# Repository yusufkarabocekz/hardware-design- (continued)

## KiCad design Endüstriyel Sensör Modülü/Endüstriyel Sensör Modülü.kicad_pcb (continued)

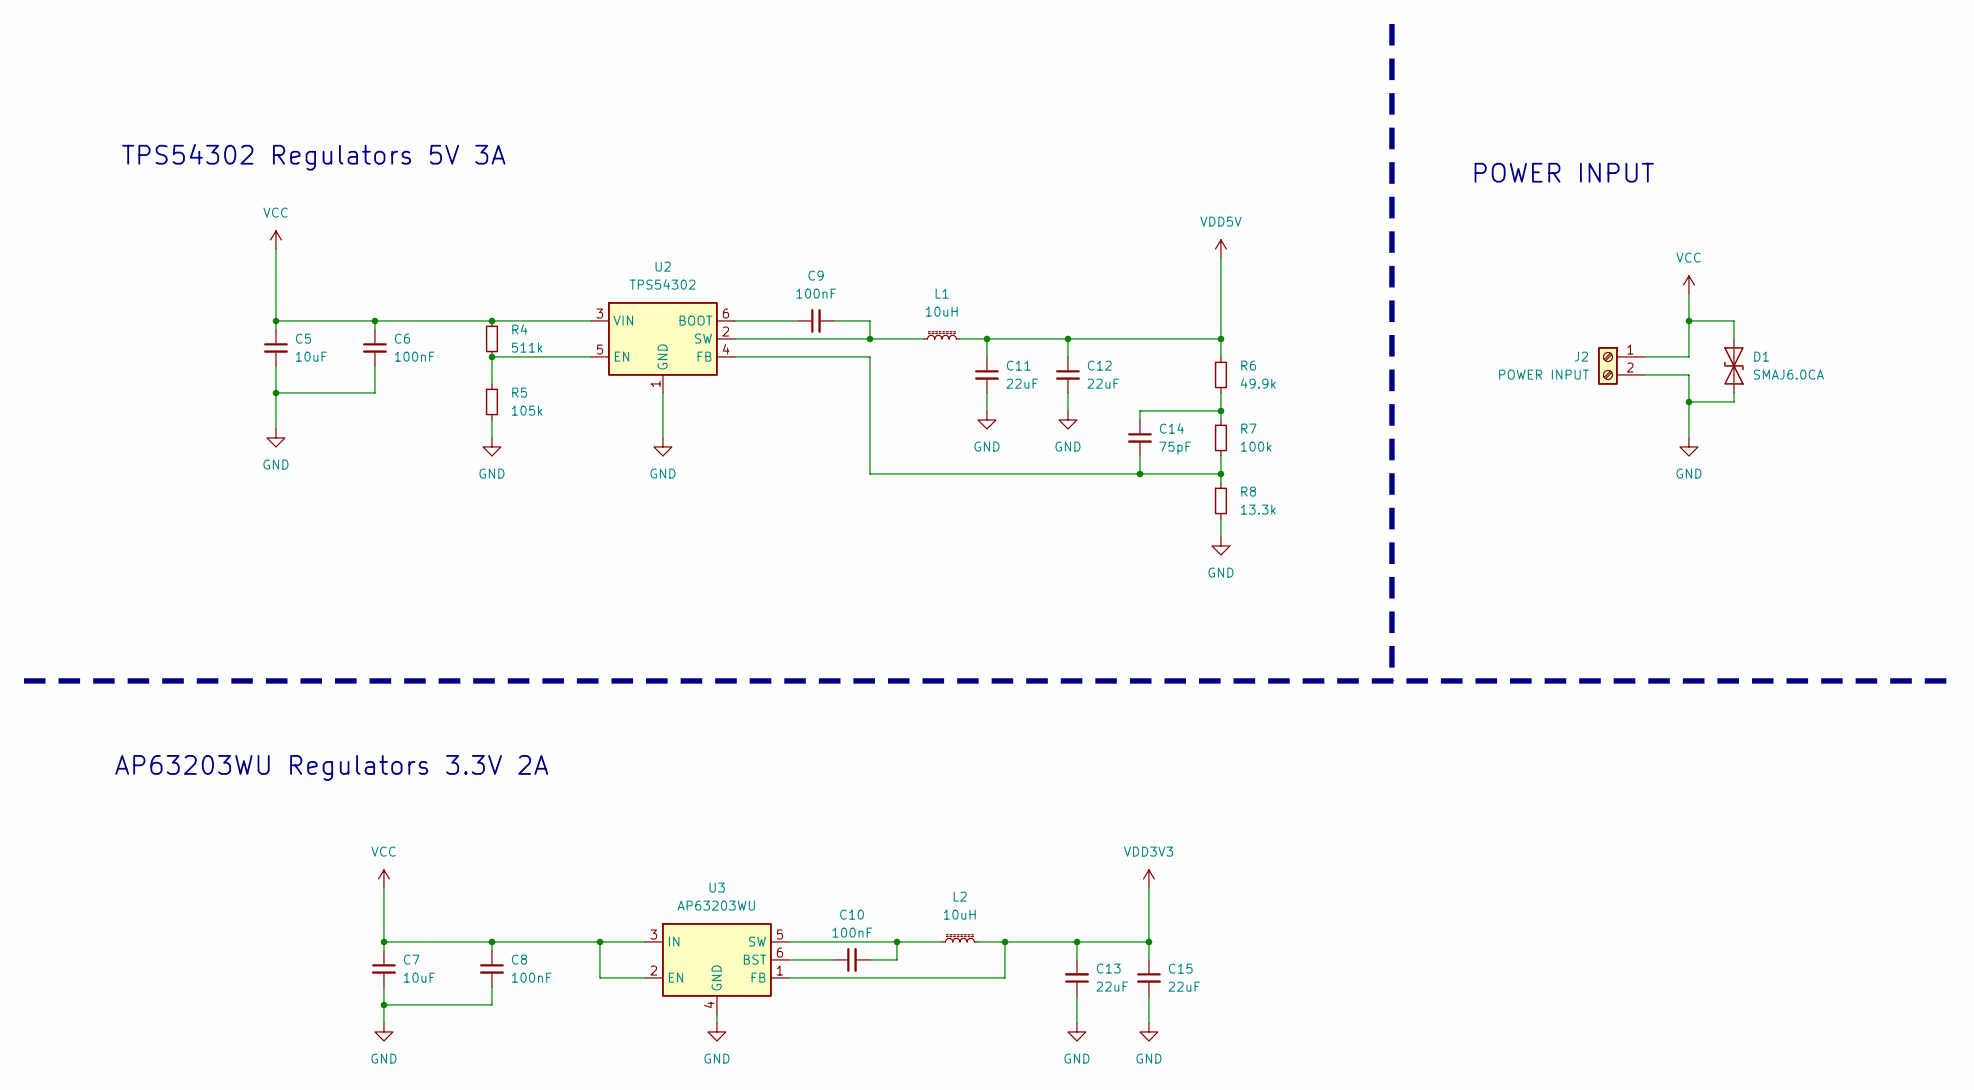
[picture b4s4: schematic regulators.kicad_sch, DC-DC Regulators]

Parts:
C5, C7: 10uF; C_0603_1608Metric
C6, C8, C9, C10: 100nF; C_0603_1608Metric
C11, C12, C13, C15: 22uF; C_0603_1608Metric
C14: 75pF; C_0603_1608Metric
D1: SMAJ6.0CA; D_SMA
J2: POWER INPUT; PhoenixContact_MSTBA_2,5_2-G-5,08_1x02_P5.08mm_Horizontal
L1, L2: 10uH; L_APV_ANR4030
R4: 511k; R_0603_1608Metric
R5: 105k; R_0603_1608Metric
R6: 49.9k; R_0603_1608Metric
R7: 100k; R_0603_1608Metric
R8: 13.3k; R_0603_1608Metric
U2: TPS54302; SOT-23-6
U3: AP63203WU; TSOT-23-6

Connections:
GND: C5.2, C6.2, C7.2, C8.2, C11.2, C12.2, C13.1, C15.2, D1.1 (A1), J2.2, R5.2, R8.2, U2.1 (GND), U3.4 (GND); also elsewhere on the board
unnamed: C14.1, R6.2, R7.1
unnamed: C9.1, U2.6 (BOOT)
unnamed: R4.2, R5.1, U2.5 (EN)
unnamed: C14.2, R7.2, R8.1, U2.4 (FB)
unnamed: C9.2, L1.1, U2.2 (SW)
unnamed: C10.1, U3.6 (BST)
unnamed: C10.2, L2.1, U3.5 (SW)
VCC: C5.1, C6.1, C7.1, C8.1, D1.2 (A2), J2.1, R4.1, U2.3 (VIN), U3.2 (EN), U3.3 (IN)
VDD3V3: C13.2, C15.1, L2.2, U3.1 (FB); also elsewhere on the board
VDD5V: C11.1, C12.1, L1.2, R6.1; also elsewhere on the board

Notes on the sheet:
TPS54302 Regulators 5V 3A
POWER INPUT
AP63203WU Regulators 3.3V 2A

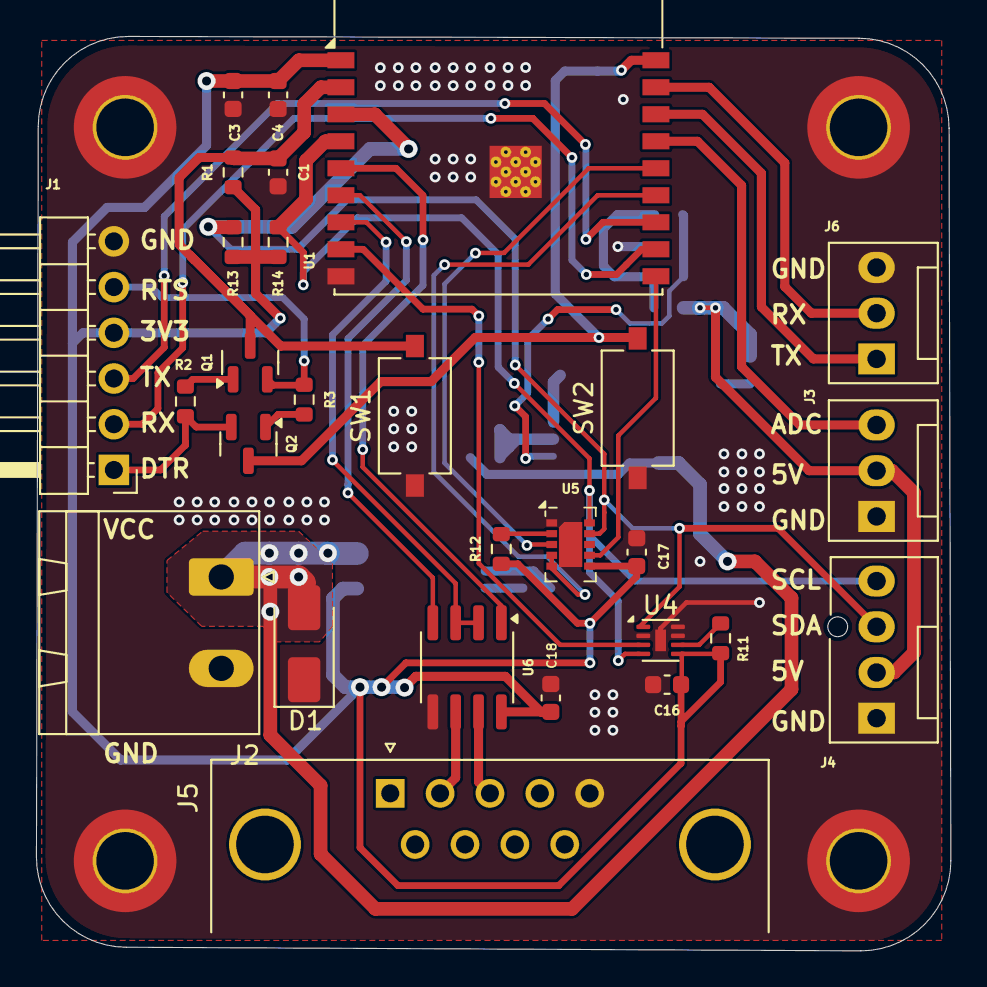
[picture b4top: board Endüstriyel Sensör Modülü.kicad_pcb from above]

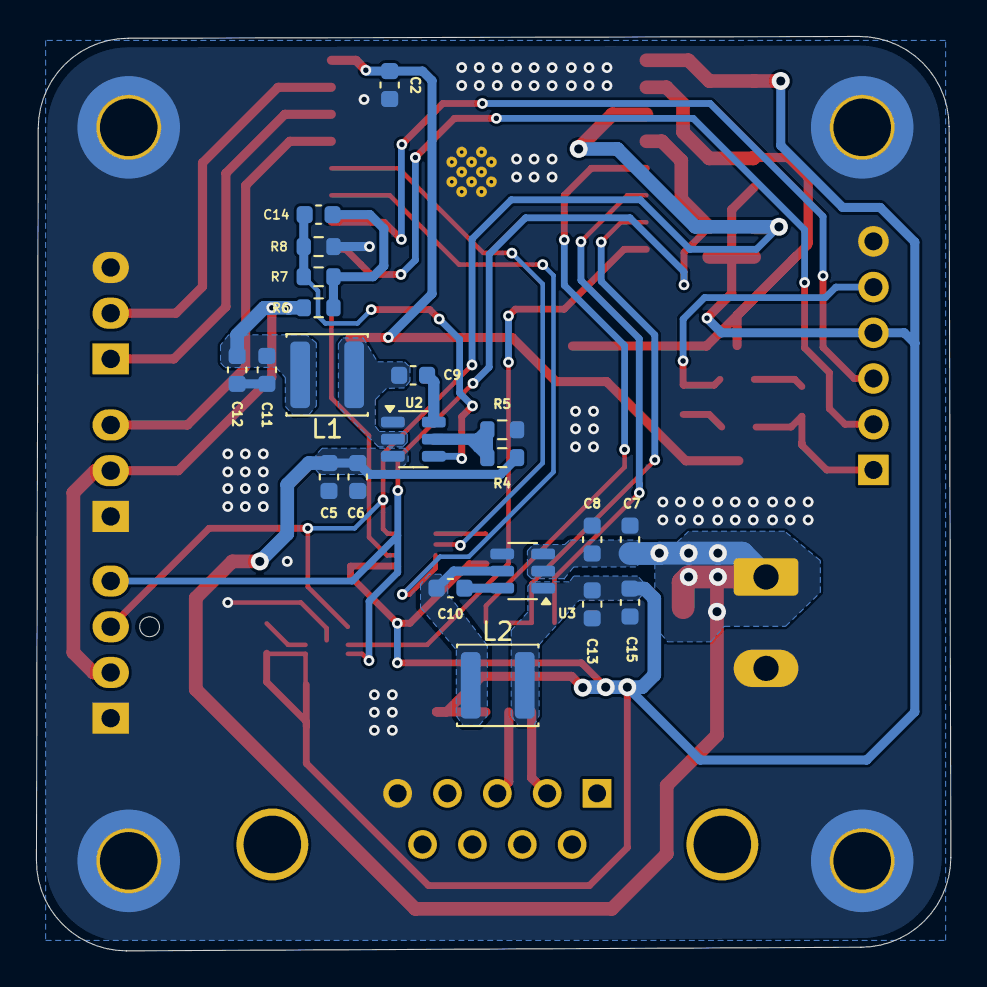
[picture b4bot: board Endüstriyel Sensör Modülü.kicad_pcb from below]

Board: 4 copper layers, 50.8 x 50.8 mm, 53 parts (21 on the bottom side), 35 nets.

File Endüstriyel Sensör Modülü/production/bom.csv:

Designator,Footprint,Quantity,Value,LCSC Part #
"C1, C17",0603,2,1uF,
"C10, C16, C18, C2, C4, C6, C8, C9",0603,8,100nF,
"C11, C12, C13, C15",0603,4,22uF,
C14,0603,1,75pF,
"C3, C5, C7",0603,3,10uF,
D1,D_SMA,1,SMAJ6.0CA,
J1,PinHeader_1x06_P2.54mm_Horizontal,1,FTDI232 Connector,
J2,"PhoenixContact_MSTBA_2,5_2-G-5,08_1x02_P5.08mm_Horizontal",1,POWER INPUT,
J3,FanPinHeader_1x03_P2.54mm_Vertical,1,ADC,
J4,FanPinHeader_1x04_P2.54mm_Vertical,1,I2C,
J5,DSUB-9_Pins_Horizontal_P2.77x2.84mm_EdgePinOffset4.94mm_Housed_MountingHolesOffset4.94mm,1,DE9_Pins,
J6,FanPinHeader_1x03_P2.54mm_Vertical,1,UART,
"L1, L2",L_APV_ANR4030,2,10uH,
"Q1, Q2",SOT-23,2,SS8050,
R1,0603,1,10k,
R11,0603,1,2k,
"R12, R13, R14",0603,3,4.7k,
"R2, R3",0603,2,12k,
R4,0603,1,511k,
R5,0603,1,105k,
R6,0603,1,49.9k,
R7,0603,1,100k,
R8,0603,1,13.3k,
SW1,SW_Tactile_SPST_NO_Straight_CK_PTS636Sx25SMTRLFS,1,RESET,
SW2,SW_Tactile_SPST_NO_Straight_CK_PTS636Sx25SMTRLFS,1,BOOT,
U1,ESP32-C3-WROOM-02,1,ESP32-C3-WROOM-02,
U2,SOT-23-6,1,TPS54302,
U3,TSOT-23-6,1,AP63203WU,
U4,DFN-8-1EP_2x2mm_P0.5mm_EP0.6x1.2mm,1,SHT31A-DIS,
U5,AMS_LGA-10-1EP_2.7x4mm_P0.6mm,1,CCS811,
U6,SOIC-8_3.9x4.9mm_P1.27mm,1,MAX485E,

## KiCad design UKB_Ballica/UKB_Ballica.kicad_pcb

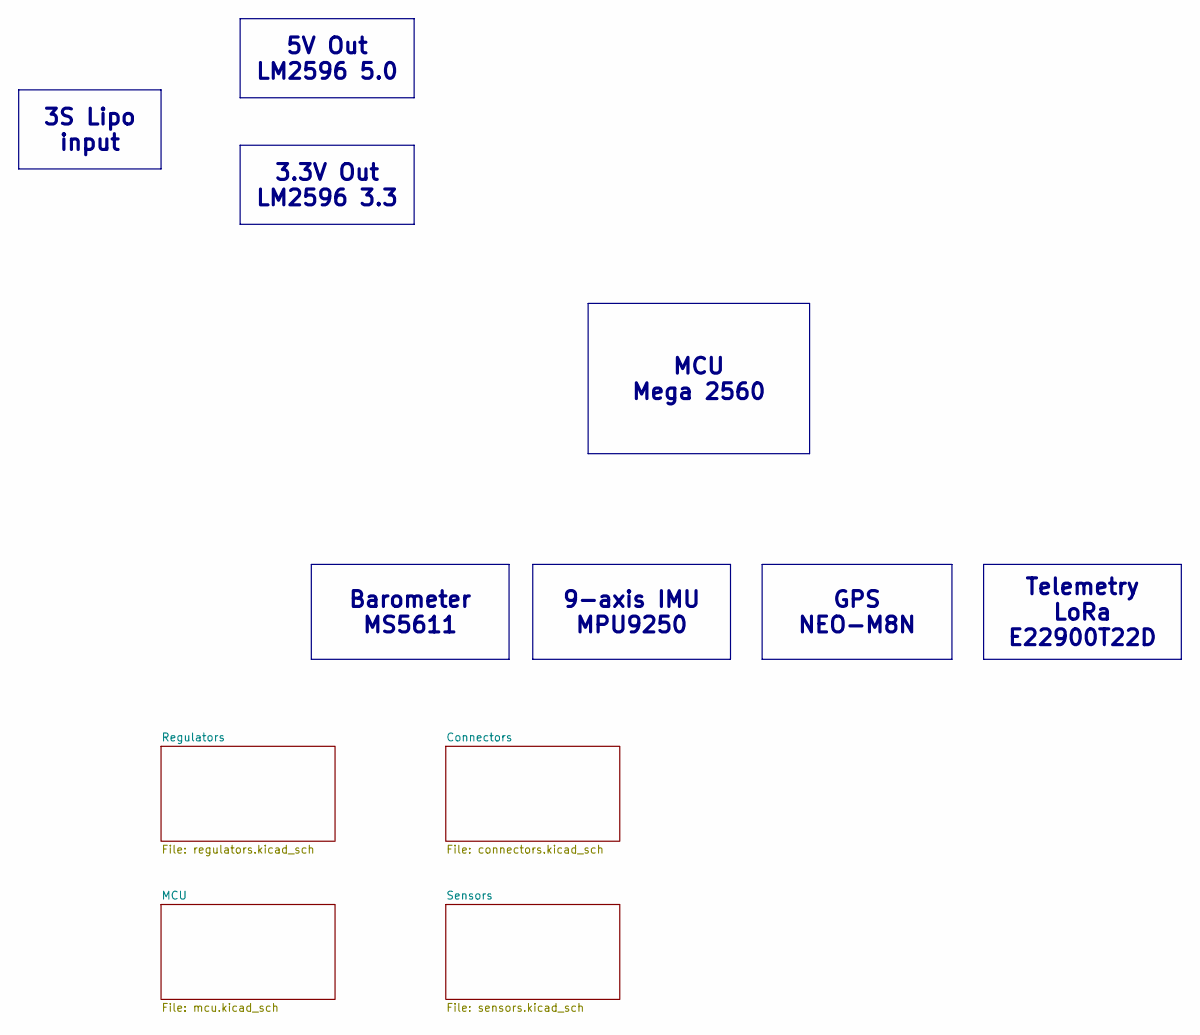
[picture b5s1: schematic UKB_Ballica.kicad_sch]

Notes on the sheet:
Telemetry LoRa E22900T22D
Barometer MS5611
GPS NEO-M8N
5V Out LM2596 5.0
9-axis IMU MPU9250
MCU Mega 2560
3S Lipo input
3.3V Out LM2596 3.3

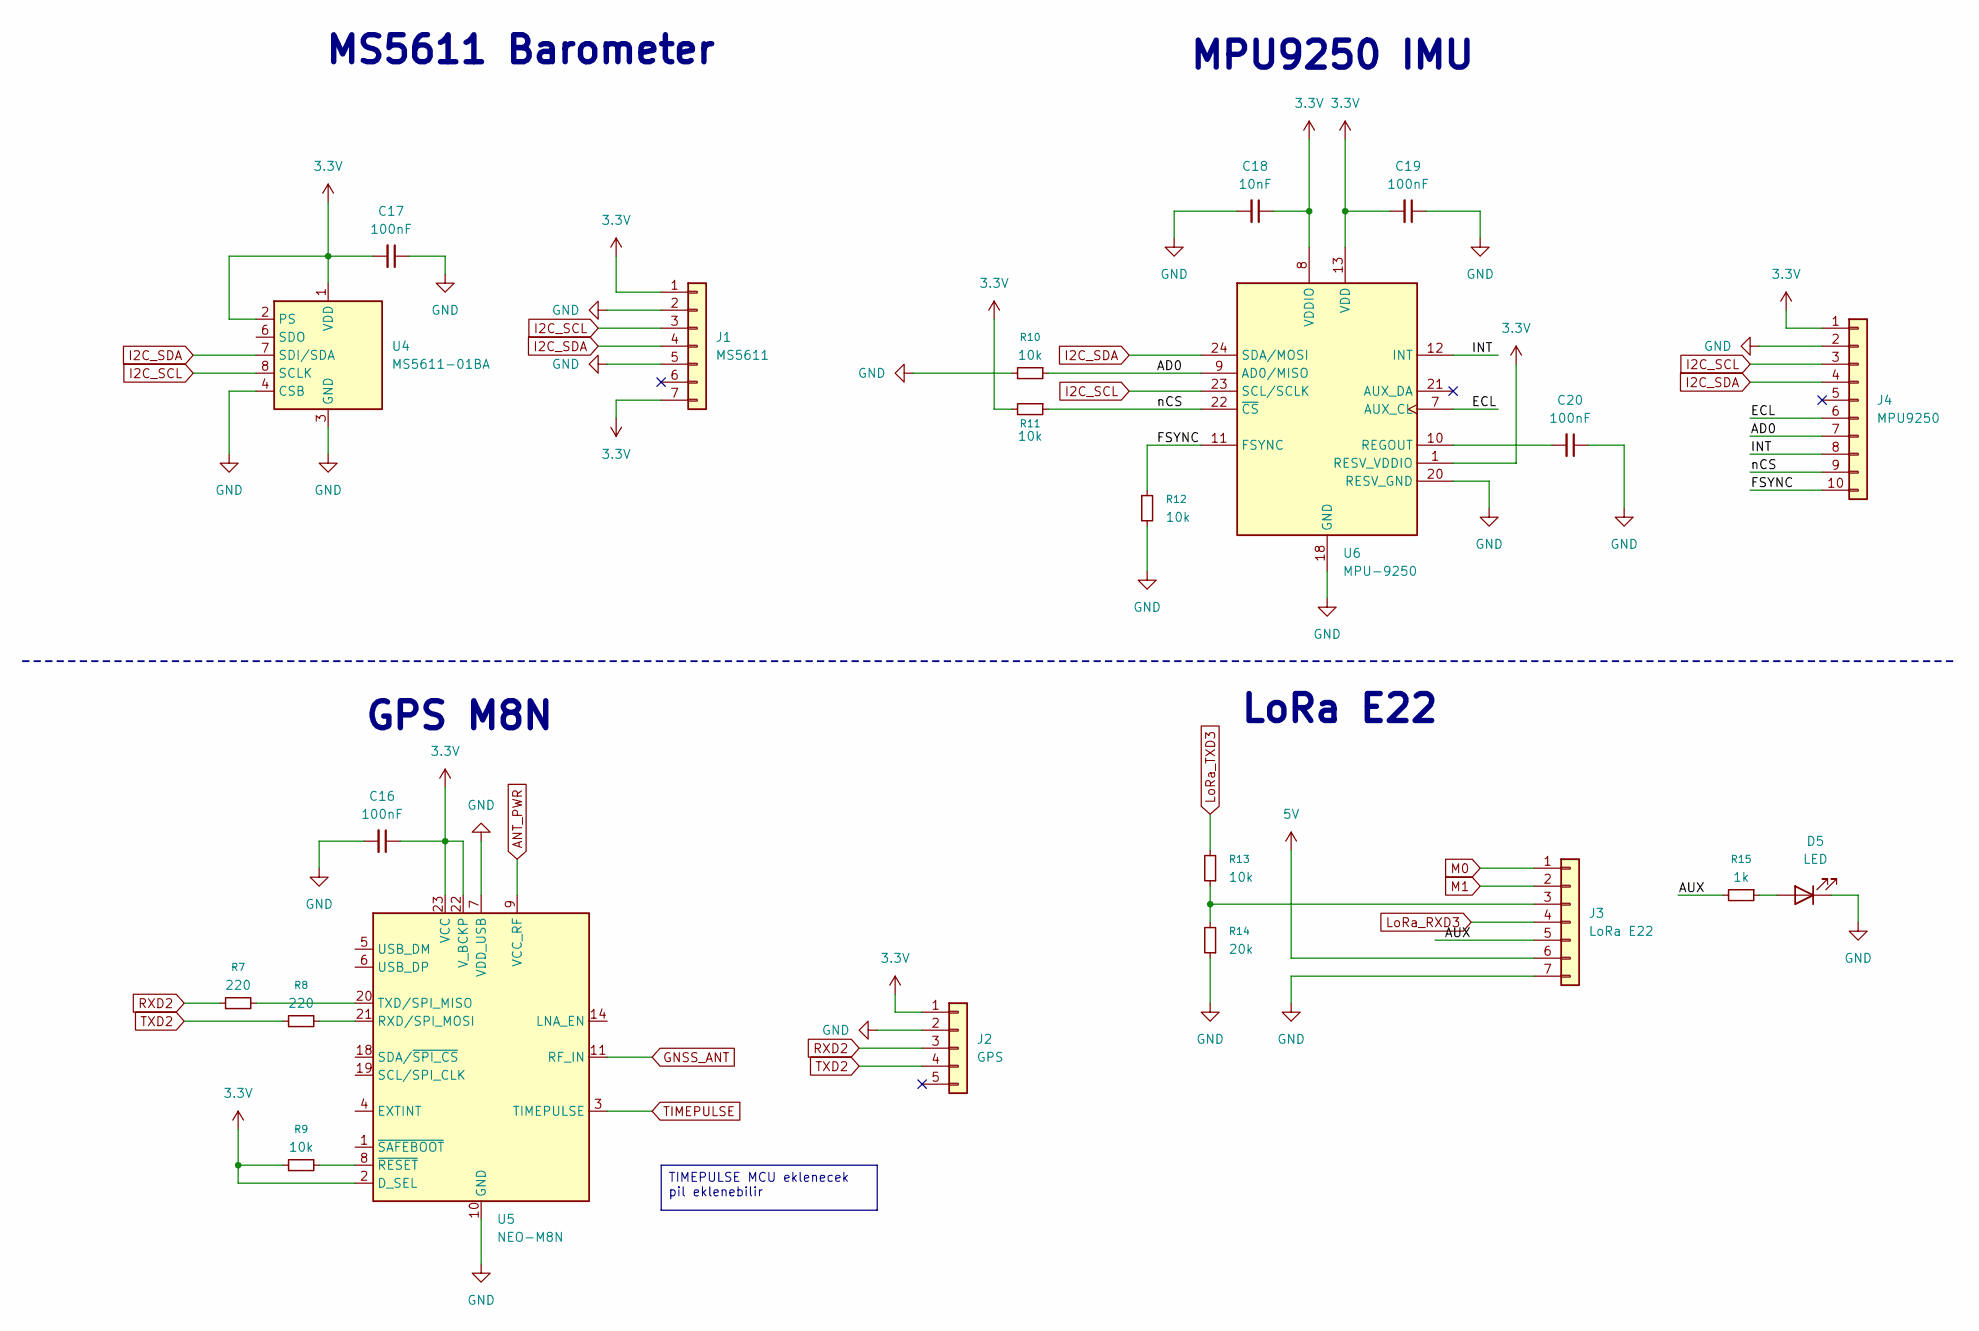
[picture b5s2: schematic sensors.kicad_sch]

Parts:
C16, C17, C19, C20: 100nF; C_0603_1608Metric_Pad1.08x0.95mm_HandSolder
C18: 10nF; C_0603_1608Metric_Pad1.08x0.95mm_HandSolder
D5: LED; LED_0603_1608Metric_Pad1.05x0.95mm_HandSolder
J1: MS5611; PinSocket_1x07_P2.54mm_Vertical
J2: GPS; PinSocket_1x05_P2.54mm_Vertical
J3: LoRa E22; PinSocket_1x07_P2.54mm_Vertical
J4: MPU9250; PinSocket_1x10_P2.54mm_Vertical
R7, R8: 220; R_0603_1608Metric_Pad0.98x0.95mm_HandSolder
R9, R10, R11, R12, R13: 10k; R_0603_1608Metric_Pad0.98x0.95mm_HandSolder
R14: 20k; R_0603_1608Metric_Pad0.98x0.95mm_HandSolder
R15: 1k; R_0603_1608Metric_Pad0.98x0.95mm_HandSolder
U4: MS5611-01BA; LGA-8_3x5mm_P1.25mm
U5: NEO-M8N; ublox_NEO
U6: MPU-9250; InvenSense_QFN-24_3x3mm_P0.4mm

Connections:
3.3V: C16.1, C17.2, C18.1, C19.2, J1.1, J1.7, J2.1, J4.1, R9.1, R11.2, U4.1 (VDD), U4.2 (PS), U5.2 (D_SEL), U5.22 (V_BCKP), U5.23 (VCC), U6.1 (RESV_VDDIO), U6.8 (VDDIO), U6.13 (VDD); also elsewhere on the board
5V: J3.6; also elsewhere on the board
/Sensors/AD0: J4.7, R10.1, U6.9 (AD0/MISO)
/Sensors/AUX: J3.5, R15.2
/Sensors/ECL: J4.6, U6.7 (AUX_CL)
/Sensors/FSYNC: J4.10, R12.1, U6.11 (FSYNC)
/Sensors/INT: J4.8, U6.12 (INT)
/Sensors/nCS: J4.9, R11.1, U6.22 (~CS)
ANT_PWR: U5.9 (VCC_RF); also elsewhere on the board
GND: C16.2, C17.1, C18.2, C19.1, C20.1, D5.1 (K), J1.2, J1.5, J2.2, J3.7, J4.2, R10.2, R12.2, R14.1, U4.3 (GND), U4.4 (CSB), U4.5 (CSB), U5.7 (VDD_USB), U5.10 (GND), U5.12 (GND), U5.13 (GND), U5.24 (GND), U6.18 (GND), U6.20 (RESV_GND); also elsewhere on the board
GNSS_ANT: U5.11 (RF_IN); also elsewhere on the board
I2C_SCL: J1.3, J4.3, U4.8 (SCLK), U6.23 (SCL/SCLK); also elsewhere on the board
I2C_SDA: J1.4, J4.4, U4.7 (SDI/SDA), U6.24 (SDA/MOSI); also elsewhere on the board
LoRa_RXD3: J3.4; also elsewhere on the board
LoRa_TXD3: R13.2; also elsewhere on the board
M0: J3.1; also elsewhere on the board
M1: J3.2; also elsewhere on the board
unnamed: D5.2 (A), R15.1
unnamed: J3.3, R13.1, R14.2
unnamed: R8.2, U5.21 (RXD/SPI_MOSI)
unnamed: R7.2, U5.20 (TXD/SPI_MISO)
unnamed: R9.2, U5.8 (~RESET)
unnamed: C20.2, U6.10 (REGOUT)
RXD2: J2.3, R7.1; also elsewhere on the board
TIMEPULSE: U5.3 (TIMEPULSE)
TXD2: J2.4, R8.1; also elsewhere on the board

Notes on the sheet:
MPU9250 IMU
LoRa E22
GPS M8N
MS5611 Barometer
TIMEPULSE MCU eklenecek pil eklenebilir

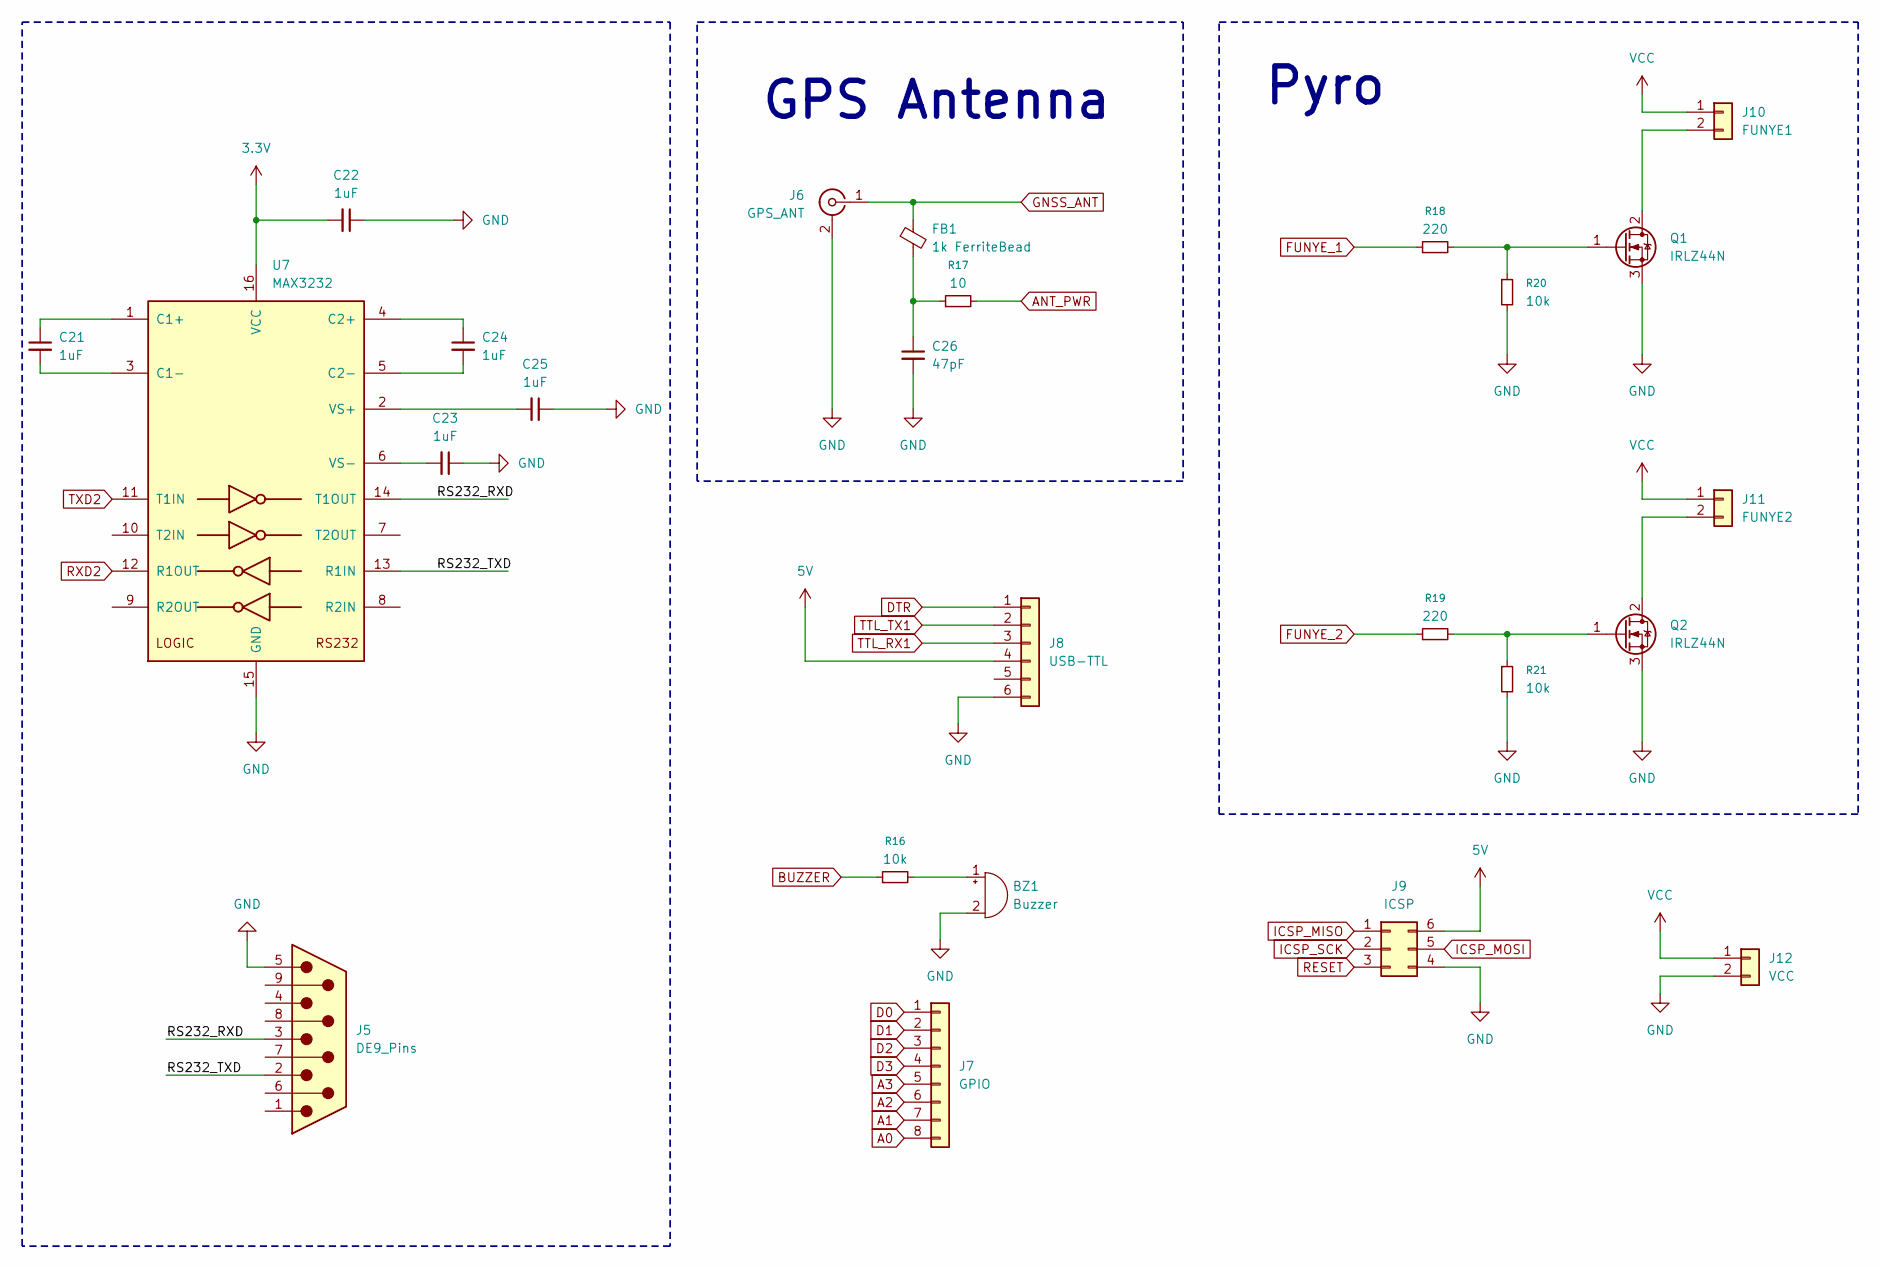
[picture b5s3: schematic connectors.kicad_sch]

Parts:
BZ1: Buzzer; Buzzer_TDK_PS1240P02BT_D12.2mm_H6.5mm
C21, C22, C23, C24, C25: 1uF; C_0603_1608Metric_Pad1.08x0.95mm_HandSolder
C26: 47pF; C_0603_1608Metric_Pad1.08x0.95mm_HandSolder
FB1: 1k FerriteBead; L_0805_2012Metric_Pad1.05x1.20mm_HandSolder
J5: DE9_Pins; DSUB-9_Socket_Vertical_P2.77x2.84mm_MountingHoles
J6: GPS_ANT; SMA_Amphenol_132134-11_Vertical
J7: GPIO; PinSocket_1x08_P2.54mm_Vertical
J8: USB-TTL; PinSocket_1x06_P2.54mm_Horizontal
J9: ICSP; PinHeader_2x03_P2.54mm_Vertical
J10: FUNYE1; TerminalBlock_Phoenix_MKDS-1,5-2_1x02_P5.00mm_Horizontal
J11: FUNYE2; TerminalBlock_Phoenix_MKDS-1,5-2_1x02_P5.00mm_Horizontal
J12: VCC; AMASS_XT30U-F_1x02_P5.0mm_Vertical
Q1, Q2: IRLZ44N; TO-220-3_Vertical
R16, R20, R21: 10k; R_0603_1608Metric_Pad0.98x0.95mm_HandSolder
R17: 10; R_0603_1608Metric_Pad0.98x0.95mm_HandSolder
R18, R19: 220; R_0603_1608Metric_Pad0.98x0.95mm_HandSolder
U7: MAX3232; SOIC-16_3.9x9.9mm_P1.27mm

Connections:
3.3V: C22.2, U7.16 (VCC); also elsewhere on the board
5V: J8.4, J9.6; also elsewhere on the board
/Connectors/RS232_RXD: J5.3, U7.14 (T1OUT)
/Connectors/RS232_TXD: J5.2, U7.13 (R1IN)
ANT_PWR: R17.2; also elsewhere on the board
BUZZER: R16.1; also elsewhere on the board
DTR: J8.1; also elsewhere on the board
FUNYE_1: R18.1; also elsewhere on the board
FUNYE_2: R19.1; also elsewhere on the board
GND: BZ1.2 (-), C22.1, C23.1, C25.1, C26.2, J5.5, J6.2 (Ext), J8.6, J9.4, J12.2, Q1.3 (S), Q2.3 (S), R20.2, R21.2, U7.15 (GND); also elsewhere on the board
GNSS_ANT: FB1.1, J6.1 (In); also elsewhere on the board
ICSP_MISO: J9.1; also elsewhere on the board
ICSP_MOSI: J9.5; also elsewhere on the board
ICSP_SCK: J9.2; also elsewhere on the board
unnamed: BZ1.1 (+), R16.2
unnamed: C26.1, FB1.2, R17.1
unnamed: J10.2, Q1.2 (D)
unnamed: J11.2, Q2.2 (D)
unnamed: Q1.1 (G), R18.2, R20.1
unnamed: Q2.1 (G), R19.2, R21.1
unnamed: C21.1, U7.1 (C1+)
unnamed: C21.2, U7.3 (C1-)
unnamed: C24.1, U7.4 (C2+)
unnamed: C24.2, U7.5 (C2-)
unnamed: C25.2, U7.2 (VS+)
unnamed: C23.2, U7.6 (VS-)
RESET: J9.3; also elsewhere on the board
RXD2: U7.12 (R1OUT); also elsewhere on the board
TTL_RX1: J8.3; also elsewhere on the board
TTL_TX1: J8.2; also elsewhere on the board
TXD2: U7.11 (T1IN); also elsewhere on the board
VCC: J10.1, J11.1, J12.1; also elsewhere on the board

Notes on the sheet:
GPS Antenna
Pyro

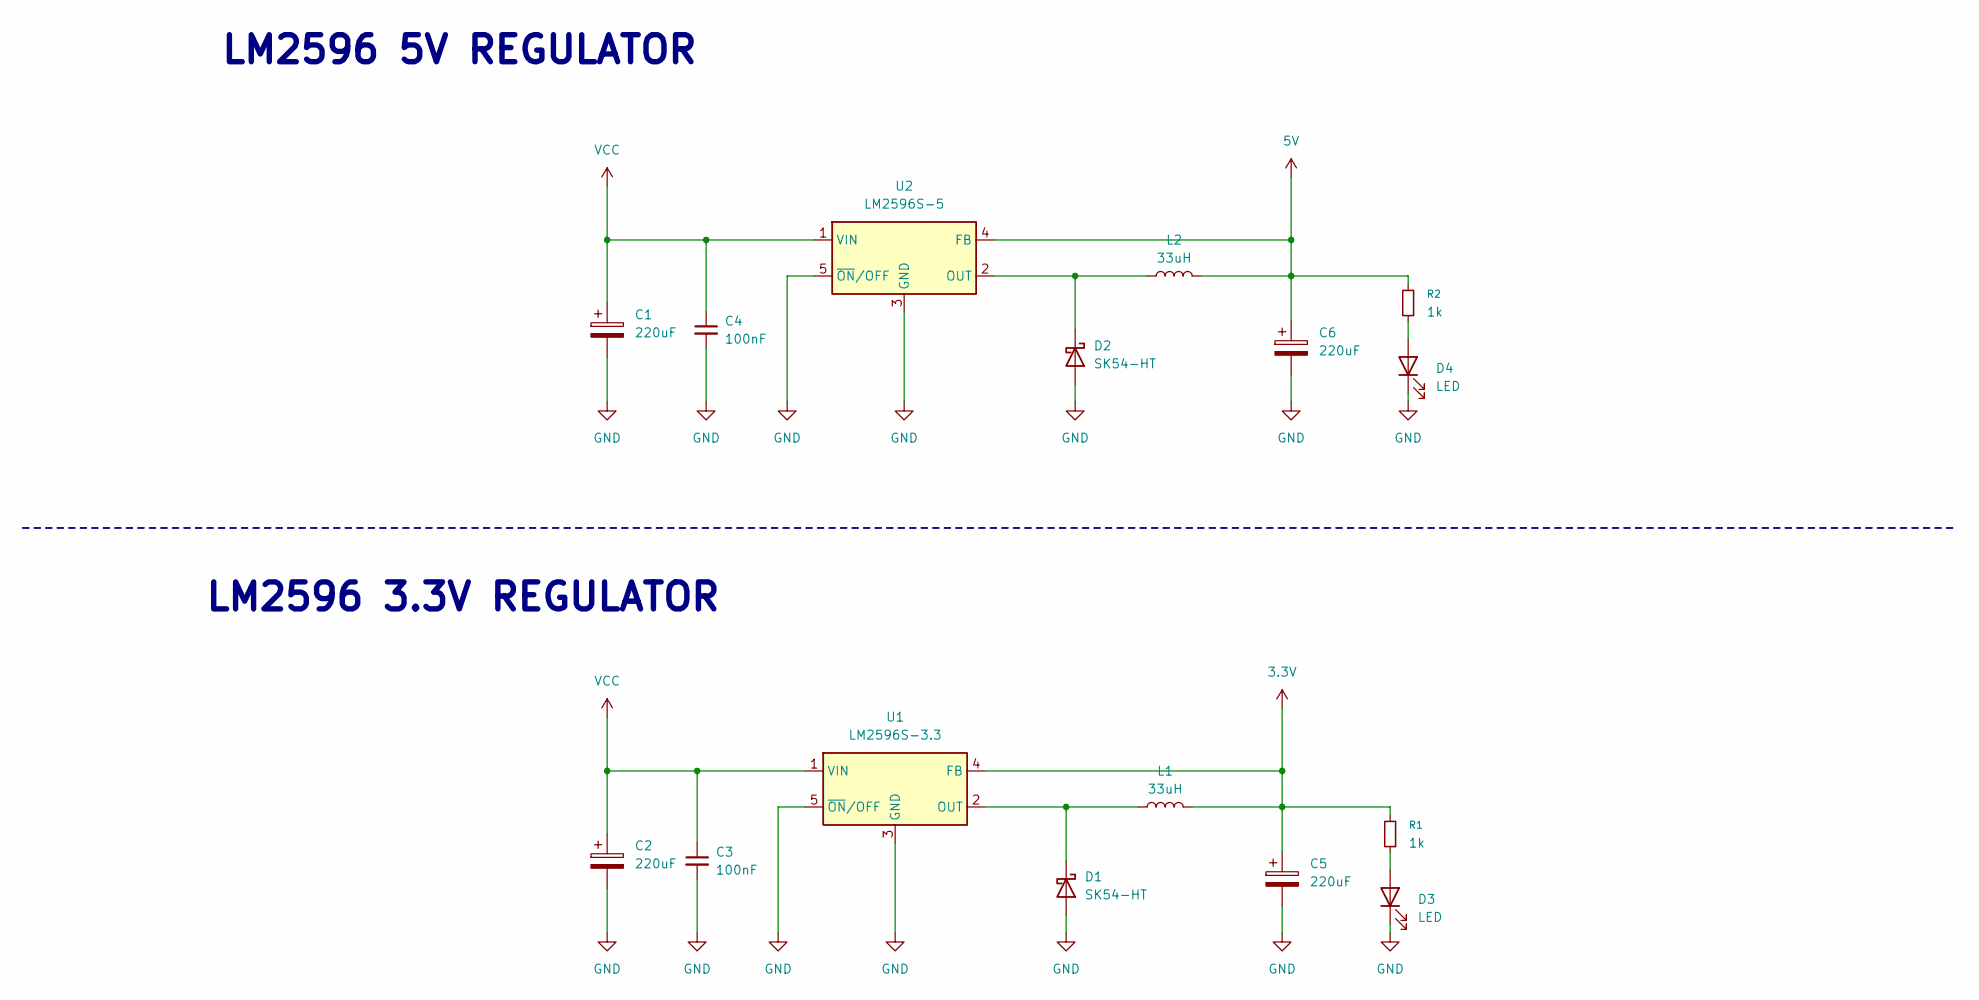
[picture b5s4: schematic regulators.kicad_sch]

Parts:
C1, C2: 220uF; CP_Elec_6.3x7.7
C3, C4: 100nF; C_0603_1608Metric_Pad1.08x0.95mm_HandSolder
C5, C6: 220uF; CP_Elec_8x10
D1, D2: SK54-HT; D_SMC_Handsoldering
D3, D4: LED; LED_0603_1608Metric_Pad1.05x0.95mm_HandSolder
L1, L2: 33uH; L_12x12mm_H6mm
R1, R2: 1k; R_0603_1608Metric_Pad0.98x0.95mm_HandSolder
U1: LM2596S-3.3; TO-263-5_TabPin3
U2: LM2596S-5; TO-263-5_TabPin3

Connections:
3.3V: C5.1, L1.2, R1.2, U1.4 (FB); also elsewhere on the board
5V: C6.1, L2.2, R2.2, U2.4 (FB); also elsewhere on the board
GND: C1.2, C2.2, C3.2, C4.2, C5.2, C6.2, D1.2 (A), D2.2 (A), D3.1 (K), D4.1 (K), U1.3 (GND), U1.5 (~ON/OFF), U2.3 (GND), U2.5 (~ON/OFF); also elsewhere on the board
unnamed: D1.1 (K), L1.1, U1.2 (OUT)
unnamed: D2.1 (K), L2.1, U2.2 (OUT)
unnamed: D3.2 (A), R1.1
unnamed: D4.2 (A), R2.1
VCC: C1.1, C2.1, C3.1, C4.1, U1.1 (VIN), U2.1 (VIN); also elsewhere on the board

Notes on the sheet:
LM2596 5V REGULATOR
LM2596 3.3V REGULATOR

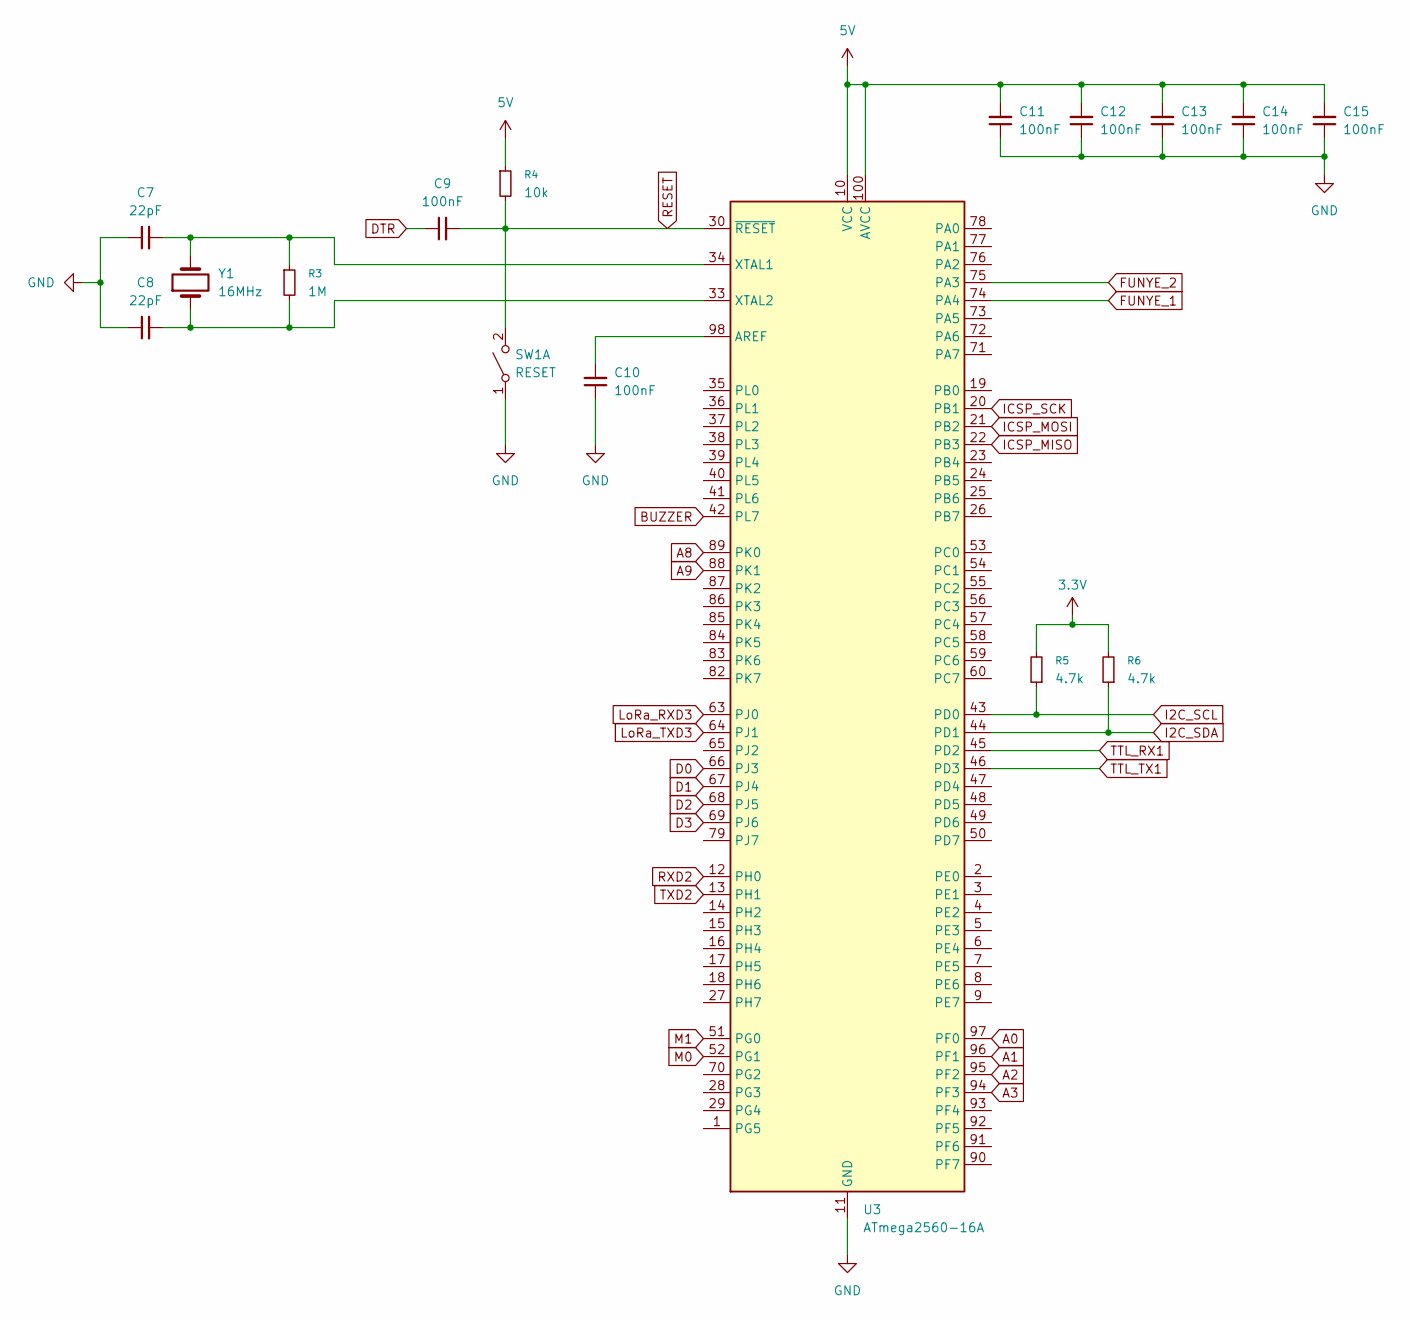
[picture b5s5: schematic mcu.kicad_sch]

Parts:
C7, C8: 22pF; C_0603_1608Metric_Pad1.08x0.95mm_HandSolder
C9, C10, C11, C12, C13, C14, C15: 100nF; C_0603_1608Metric_Pad1.08x0.95mm_HandSolder
R3: 1M; R_0603_1608Metric_Pad0.98x0.95mm_HandSolder
R4: 10k; R_0603_1608Metric_Pad0.98x0.95mm_HandSolder
R5, R6: 4.7k; R_0603_1608Metric_Pad0.98x0.95mm_HandSolder
SW1: RESET; SW_PUSH_6mm_H5mm
U3: ATmega2560-16A; TQFP-100_14x14mm_P0.5mm
Y1: 16MHz; Crystal_HC49-4H_Vertical

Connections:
3.3V: R5.2, R6.2; also elsewhere on the board
5V: C11.2, C12.2, C13.2, C14.2, C15.2, R4.1, U3.10 (VCC), U3.31 (VCC), U3.61 (VCC), U3.80 (VCC), U3.100 (AVCC); also elsewhere on the board
A0: U3.97 (PF0)
A1: U3.96 (PF1)
A2: U3.95 (PF2)
A3: U3.94 (PF3)
A8: U3.89 (PK0)
A9: U3.88 (PK1)
BUZZER: U3.42 (PL7); also elsewhere on the board
D0: U3.66 (PJ3)
D1: U3.67 (PJ4)
D2: U3.68 (PJ5)
D3: U3.69 (PJ6)
DTR: C9.1; also elsewhere on the board
FUNYE_1: U3.74 (PA4); also elsewhere on the board
FUNYE_2: U3.75 (PA3); also elsewhere on the board
GND: C7.1, C8.1, C10.1, C11.1, C12.1, C13.1, C14.1, C15.1, SW1.1 (A), U3.11 (GND), U3.32 (GND), U3.62 (GND), U3.81 (GND), U3.99 (GND); also elsewhere on the board
I2C_SCL: R5.1, U3.43 (PD0); also elsewhere on the board
I2C_SDA: R6.1, U3.44 (PD1); also elsewhere on the board
ICSP_MISO: U3.22 (PB3); also elsewhere on the board
ICSP_MOSI: U3.21 (PB2); also elsewhere on the board
ICSP_SCK: U3.20 (PB1); also elsewhere on the board
LoRa_RXD3: U3.63 (PJ0); also elsewhere on the board
LoRa_TXD3: U3.64 (PJ1); also elsewhere on the board
M0: U3.52 (PG1); also elsewhere on the board
M1: U3.51 (PG0); also elsewhere on the board
unnamed: C10.2, U3.98 (AREF)
unnamed: C7.2, R3.1, U3.34 (XTAL1), Y1.2
unnamed: C8.2, R3.2, U3.33 (XTAL2), Y1.1
RESET: C9.2, R4.2, SW1.2 (B), U3.30 (~RESET); also elsewhere on the board
RXD2: U3.12 (PH0); also elsewhere on the board
TTL_RX1: U3.45 (PD2); also elsewhere on the board
TTL_TX1: U3.46 (PD3); also elsewhere on the board
TXD2: U3.13 (PH1); also elsewhere on the board

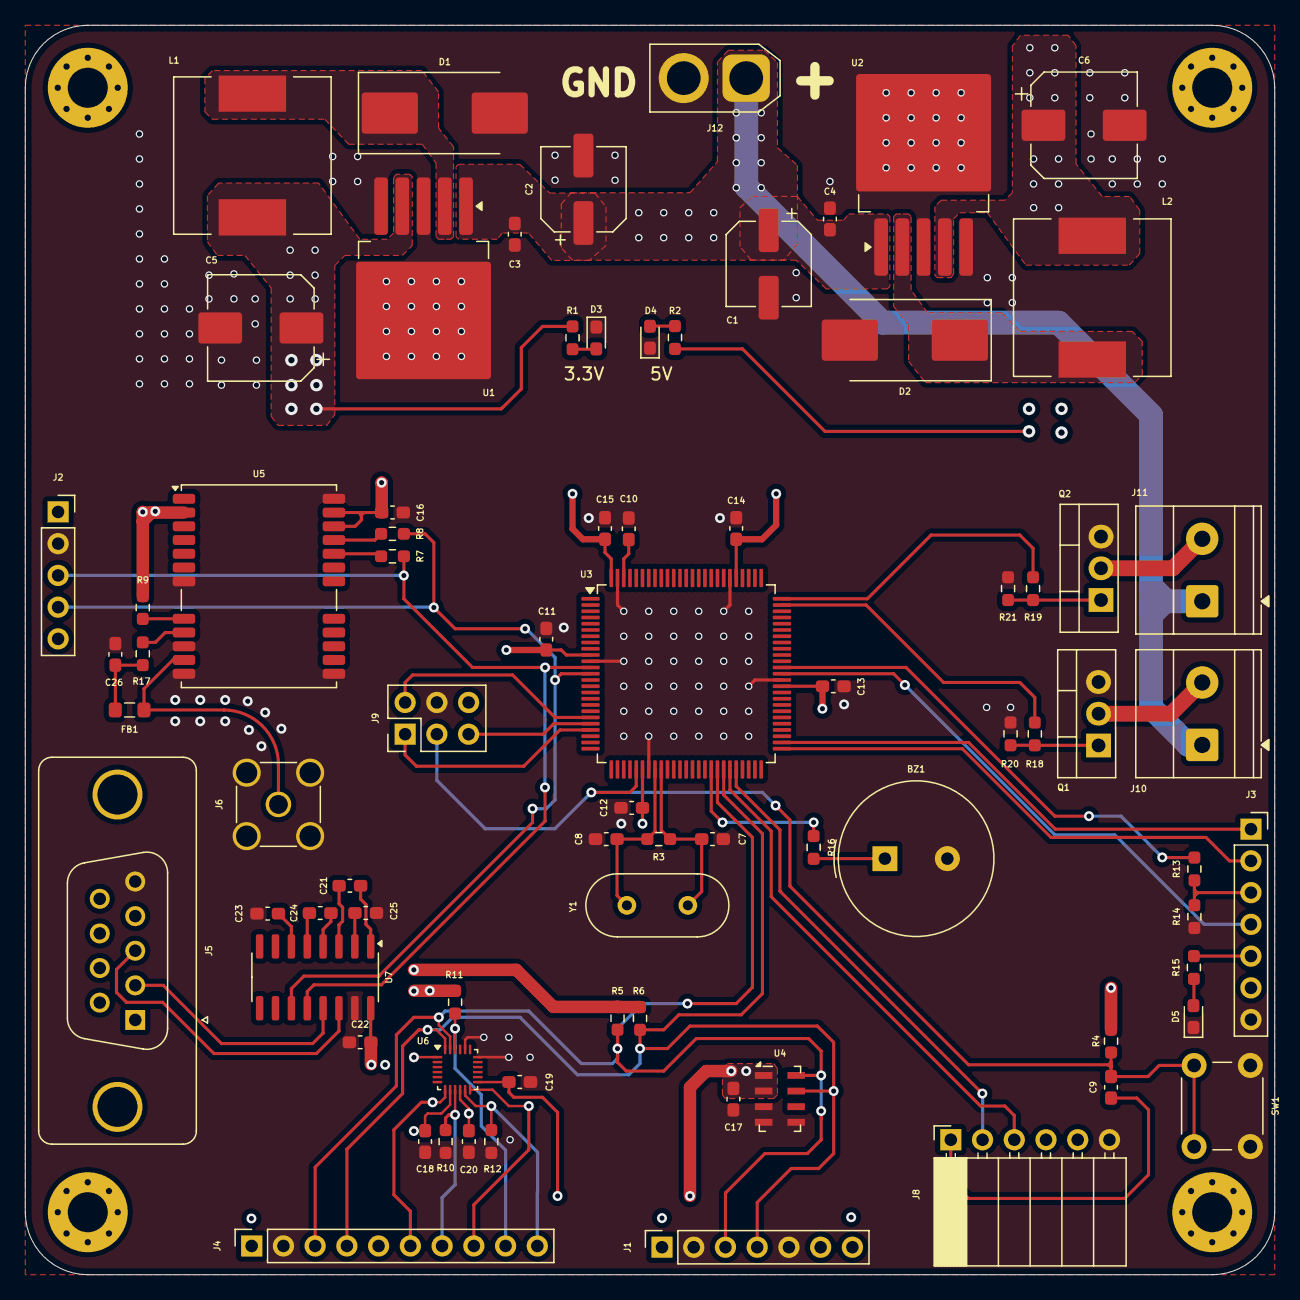
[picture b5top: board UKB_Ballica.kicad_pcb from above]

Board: 4 copper layers, 100.0 x 100.0 mm, 78 parts (0 on the bottom side), 57 nets.

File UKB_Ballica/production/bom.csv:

Designator,Footprint,Quantity,Value,LCSC Part #
BZ1,Buzzer_TDK_PS1240P02BT_D12.2mm_H6.5mm,1,Buzzer,
"C1, C2",CP_Elec_6.3x7.7,2,220uF,
"C10, C11, C12, C13, C14, C15, C16, C17, C19, C20, C3, C4, C9",0603,13,100nF,
C18,0603,1,10nF,
"C21, C22, C23, C24, C25",0603,5,1uF,
C26,0603,1,47pF,
"C5, C6",CP_Elec_8x10,2,220uF,
"C7, C8",0603,2,22pF,
"D1, D2",D_SMC_Handsoldering,2,SK54-HT,
"D3, D4, D5",0603,3,LED,
FB1,0805,1,1k FerriteBead,
J1,PinSocket_1x07_P2.54mm_Vertical,1,MS5611,
J10,"TerminalBlock_Phoenix_MKDS-1,5-2_1x02_P5.00mm_Horizontal",1,FUNYE1,
J11,"TerminalBlock_Phoenix_MKDS-1,5-2_1x02_P5.00mm_Horizontal",1,FUNYE2,
J12,AMASS_XT30U-F_1x02_P5.0mm_Vertical,1,VCC,
J2,PinSocket_1x05_P2.54mm_Vertical,1,GPS,
J3,PinSocket_1x07_P2.54mm_Vertical,1,LoRa E22,
J4,PinSocket_1x10_P2.54mm_Vertical,1,MPU9250,
J5,DSUB-9_Socket_Vertical_P2.77x2.84mm_MountingHoles,1,DE9_Pins,
J6,SMA_Amphenol_132134-11_Vertical,1,GPS_ANT,
J8,PinSocket_1x06_P2.54mm_Horizontal,1,USB-TTL,
J9,PinHeader_2x03_P2.54mm_Vertical,1,ICSP,
"L1, L2",L_12x12mm_H6mm,2,33uH,
"Q1, Q2",TO-220-3_Vertical,2,IRLZ44N,
"R1, R15, R2",0603,3,1k,
"R10, R11, R12, R13, R16, R20, R21, R4, R9",0603,9,10k,
R14,0603,1,20k,
R17,0603,1,10,
"R18, R19, R7, R8",0603,4,220,
R3,0603,1,1M,
"R5, R6",0603,2,4.7k,
SW1,SW_PUSH_6mm_H5mm,1,RESET,
U1,TO-263-5_TabPin3,1,LM2596S-3.3,
U2,TO-263-5_TabPin3,1,LM2596S-5,
U3,TQFP-100_14x14mm_P0.5mm,1,ATmega2560-16A,
U4,LGA-8_3x5mm_P1.25mm,1,MS5611-01BA,
U5,ublox_NEO,1,NEO-M8N,
U6,InvenSense_QFN-24_3x3mm_P0.4mm,1,MPU-9250,
U7,SOIC-16_3.9x9.9mm_P1.27mm,1,MAX3232,
Y1,Crystal_HC49-4H_Vertical,1,16MHz,
